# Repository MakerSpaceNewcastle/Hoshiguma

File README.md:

# Hoshiguma

Maker Space's shiny new laser cutter.

Docs Soon(TM).

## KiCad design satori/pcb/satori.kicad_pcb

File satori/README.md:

# Satori

This coprocessor is responsible for slow, low priority or unreliable machine safety signalling and networked reporting.

## Tasks

- Read cooling system temperature sensors
- Read cooling system flow sensor
- Receive machine status from Koishi via UART
- Report complete machine status and sensor values via MQTT

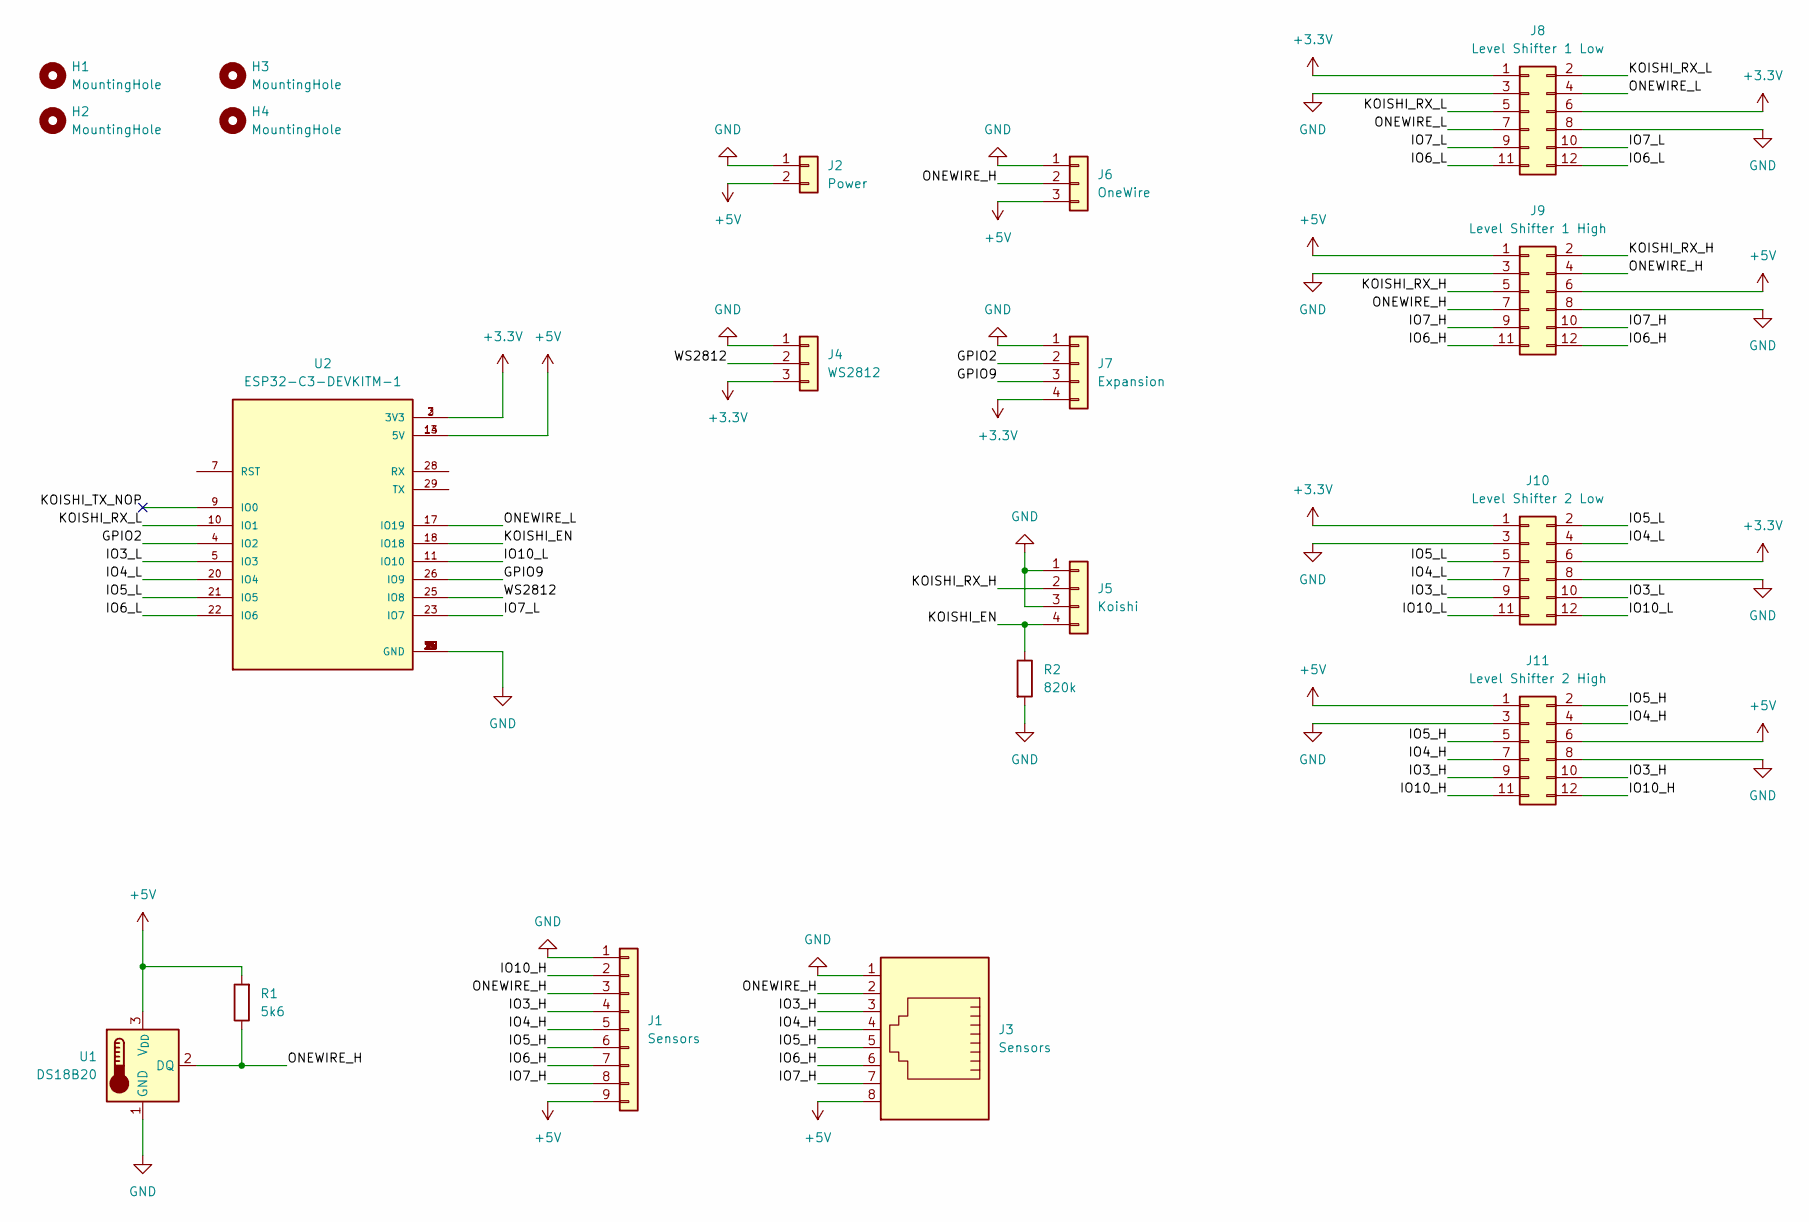
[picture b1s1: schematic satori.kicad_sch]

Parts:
H1, H2, H3, H4: MountingHole; MountingHole_3.2mm_M3
J1: Sensors; PinHeader_1x09_P2.54mm_Vertical
J2: Power; PinHeader_1x02_P2.54mm_Vertical
J3: Sensors; RJ45_Amphenol_54602-x08_Horizontal
J4: WS2812; PinHeader_1x03_P2.54mm_Vertical
J5: Koishi; PinHeader_1x04_P2.54mm_Vertical
J6: OneWire; PinHeader_1x03_P2.54mm_Vertical
J7: Expansion; PinHeader_1x04_P2.54mm_Vertical
J8: Level Shifter 1 Low; PinSocket_2x06_P2.54mm_Vertical
J9: Level Shifter 1 High; PinSocket_2x06_P2.54mm_Vertical
J10: Level Shifter 2 Low; PinSocket_2x06_P2.54mm_Vertical
J11: Level Shifter 2 High; PinSocket_2x06_P2.54mm_Vertical
R1: 5k6; R_Axial_DIN0207_L6.3mm_D2.5mm_P7.62mm_Horizontal
R2: 820k; R_Axial_DIN0207_L6.3mm_D2.5mm_P7.62mm_Horizontal
U1: DS18B20; TO-92_Inline
U2: ESP32-C3-DEVKITM-1; XCVR_ESP32-C3-DEVKITM-1

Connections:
+3.3V: J4.3, J7.4, J8.1, J8.6, J10.1, J10.6, U2.2 (3V3), U2.3 (3V3)
+5V: J1.9, J2.2, J3.8, J6.3, J9.1, J9.6, J11.1, J11.6, R1.2, U1.3 (V_{DD}), U2.13 (5V), U2.14 (5V)
/GPIO2: J7.2, U2.4 (IO2)
/GPIO9: J7.3, U2.26 (IO9)
/IO3_H: J1.4, J3.3, J11.9, J11.10
/IO3_L: J10.9, J10.10, U2.5 (IO3)
/IO4_H: J1.5, J3.4, J11.4, J11.7
/IO4_L: J10.4, J10.7, U2.20 (IO4)
/IO5_H: J1.6, J3.5, J11.2, J11.5
/IO5_L: J10.2, J10.5, U2.21 (IO5)
/IO6_H: J1.7, J3.6, J9.11, J9.12
/IO6_L: J8.11, J8.12, U2.22 (IO6)
/IO7_H: J1.8, J3.7, J9.9, J9.10
/IO7_L: J8.9, J8.10, U2.23 (IO7)
/IO10_H: J1.2, J11.11, J11.12
/IO10_L: J10.11, J10.12, U2.11 (IO10)
/KOISHI_EN: J5.4, R2.1, U2.18 (IO18)
/KOISHI_RX_H: J5.2, J9.2, J9.5
/KOISHI_RX_L: J8.2, J8.5, U2.10 (IO1)
/KOISHI_TX_NOP: U2.9 (IO0)
/ONEWIRE_H: J1.3, J3.2, J6.2, J9.4, J9.7, R1.1, U1.2 (DQ)
/ONEWIRE_L: J8.4, J8.7, U2.17 (IO19)
/WS2812: J4.2, U2.25 (IO8)
GND: J1.1, J2.1, J3.1, J4.1, J5.1, J5.3, J6.1, J7.1, J8.3, J8.8, J9.3, J9.8, J10.3, J10.8, J11.3, J11.8, R2.2, U1.1 (GND), U2.1 (GND), U2.6 (GND), U2.8 (GND), U2.12 (GND), U2.15 (GND), U2.16 (GND), U2.19 (GND), U2.24 (GND), U2.27 (GND), U2.30 (GND)

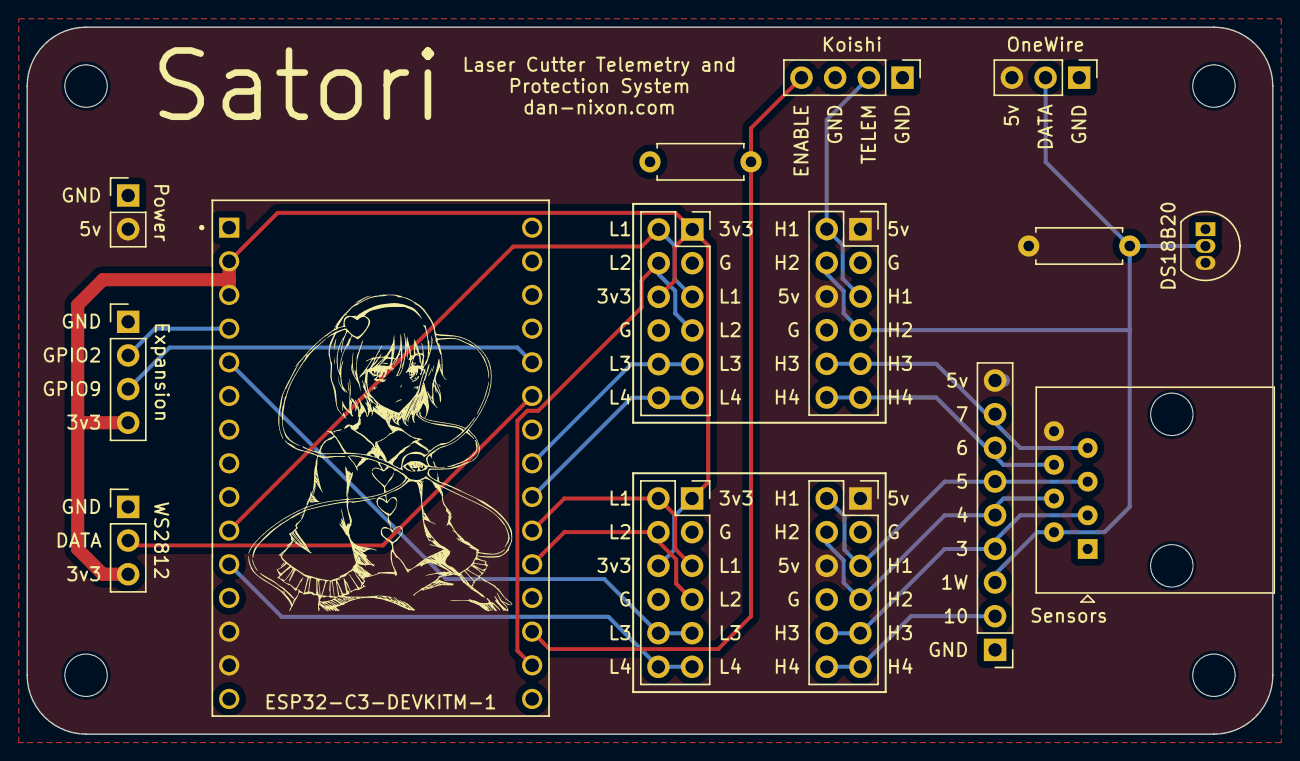
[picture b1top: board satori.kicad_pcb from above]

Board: 2 copper layers, 94.0 x 53.3 mm, 19 parts (0 on the bottom side), 23 nets.

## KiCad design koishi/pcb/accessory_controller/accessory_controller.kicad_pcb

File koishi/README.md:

# Koishi

This coprocessor is responsible for fast safety and machine control signalling only.

All inputs are via isolated digital pins. Serial input should not be used.

Outputs are via relays and status reporting via UART.

## Tasks

- Providing Ruida generic system protection signal
- Providing Ruida cooling protection signal
- Providing laser PSU protection signal
- Start/stop air assist compressor
- Start/stop fume extraction fan
- Illuminate machine status lights

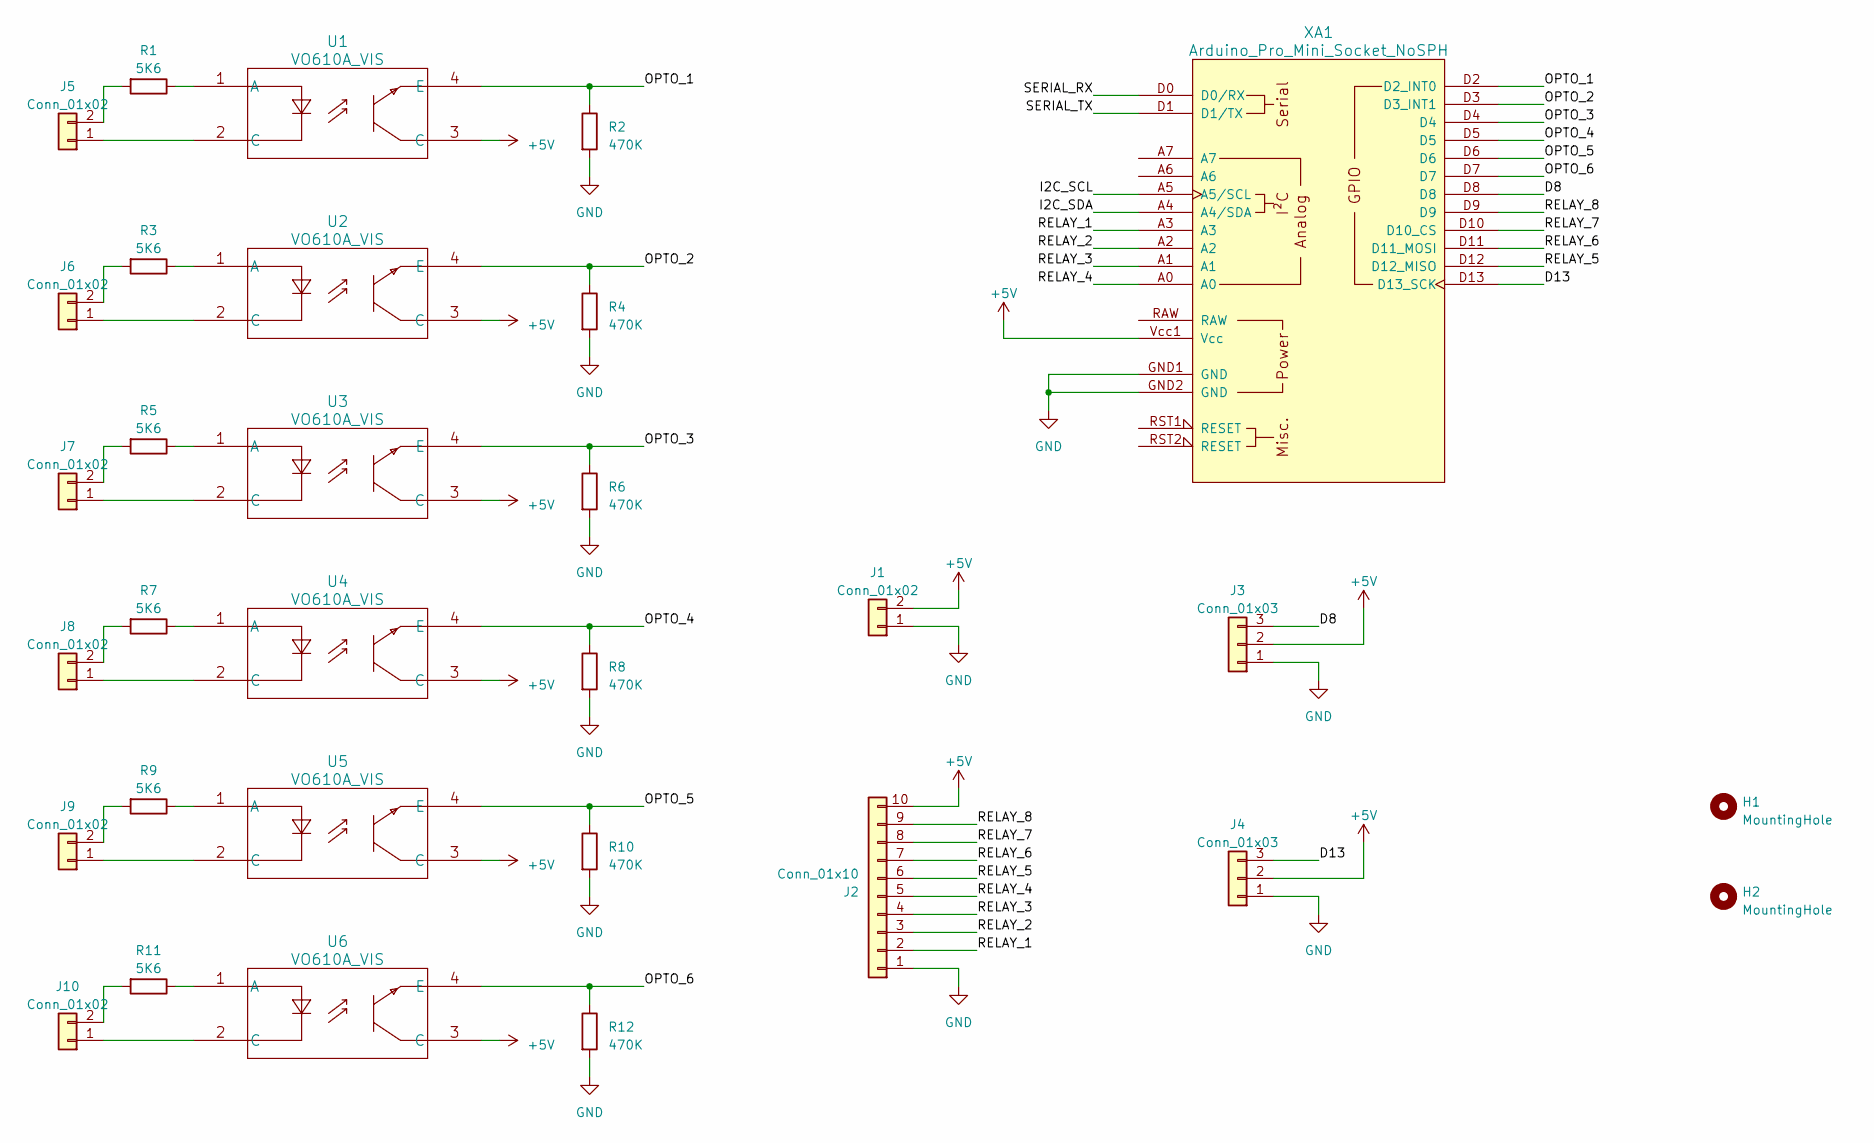
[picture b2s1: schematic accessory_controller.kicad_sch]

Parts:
H1, H2: MountingHole; MountingHole_4mm
J1, J5, J6, J7, J8, J9, J10: Conn_01x02; PinHeader_1x02_P2.54mm_Vertical
J2: Conn_01x10; PinSocket_1x10_P2.54mm_Vertical
J3, J4: Conn_01x03; PinHeader_1x03_P2.54mm_Vertical
R1, R3, R5, R7, R9, R11: 5K6; R_Axial_DIN0207_L6.3mm_D2.5mm_P2.54mm_Vertical
R2, R4, R6, R8, R10, R12: 470K; R_Axial_DIN0207_L6.3mm_D2.5mm_P2.54mm_Vertical
U1, U2, U3, U4, U5, U6: VO610A_VIS; VO610A-3
XA1: Arduino_Pro_Mini_Socket_NoSPH

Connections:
+5V: J1.2, J2.10, J3.2, J4.2, U1.3 (C), U2.3 (C), U3.3 (C), U4.3 (C), U5.3 (C), U6.3 (C), XA1.Vcc1 (Vcc)
/D8: J3.3, XA1.D8
/D13: J4.3, XA1.D13 (D13_SCK)
/I2C_SCL: XA1.A5 (A5/SCL)
/I2C_SDA: XA1.A4 (A4/SDA)
/OPTO_1: R2.1, U1.4 (E), XA1.D2 (D2_INT0)
/OPTO_2: R4.1, U2.4 (E), XA1.D3 (D3_INT1)
/OPTO_3: R6.1, U3.4 (E), XA1.D4
/OPTO_4: R8.1, U4.4 (E), XA1.D5
/OPTO_5: R10.1, U5.4 (E), XA1.D6
/OPTO_6: R12.1, U6.4 (E), XA1.D7
/RELAY_1: J2.2, XA1.A3
/RELAY_2: J2.3, XA1.A2
/RELAY_3: J2.4, XA1.A1
/RELAY_4: J2.5, XA1.A0
/RELAY_5: J2.6, XA1.D12 (D12_MISO)
/RELAY_6: J2.7, XA1.D11 (D11_MOSI)
/RELAY_7: J2.8, XA1.D10 (D10_CS)
/RELAY_8: J2.9, XA1.D9
/SERIAL_RX: XA1.D0 (D0/RX)
/SERIAL_TX: XA1.D1 (D1/TX)
GND: J1.1, J2.1, J3.1, J4.1, R2.2, R4.2, R6.2, R8.2, R10.2, R12.2, XA1.GND1 (GND), XA1.GND2 (GND)
unnamed: J5.1, U1.2 (C)
unnamed: J5.2, R1.2
unnamed: J6.1, U2.2 (C)
unnamed: J6.2, R3.2
unnamed: J7.1, U3.2 (C)
unnamed: J7.2, R5.2
unnamed: J8.1, U4.2 (C)
unnamed: J8.2, R7.2
unnamed: J9.1, U5.2 (C)
unnamed: J9.2, R9.2
unnamed: J10.1, U6.2 (C)
unnamed: J10.2, R11.2
unnamed: R1.1, U1.1 (A)
unnamed: R3.1, U2.1 (A)
unnamed: R5.1, U3.1 (A)
unnamed: R7.1, U4.1 (A)
unnamed: R9.1, U5.1 (A)
unnamed: R11.1, U6.1 (A)

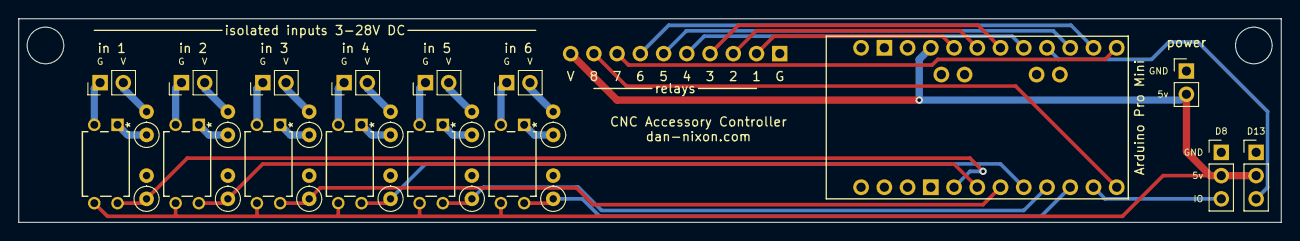
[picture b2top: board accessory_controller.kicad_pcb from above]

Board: 2 copper layers, 138.0 x 22.3 mm, 31 parts (1 on the bottom side), 36 nets.

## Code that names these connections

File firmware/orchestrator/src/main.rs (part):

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        relay: PIN_13, // Relay 6
    },
    unused_relays: UnusedRelayResources {
        relay_3: PIN_10,
        relay_7: PIN_14,
        relay_8: PIN_15,
    },
}

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
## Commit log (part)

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2025-10-01 build(deps): bump sntpc
    Bumps the cargo-dependencies group in /telemetry-module-firmware with 1 update: [sntpc](https://github.com/vpetrigo/sntpc).
    Updates `sntpc` from 0.6.0 to 0.6.1
    - [Release notes](https://github.com/vpetrigo/sntpc/releases)
    - [Commits](https://github.com/vpetrigo/sntpc/compare/v0.6.0...v0.6.1)
    ---
    updated-dependencies:
2025-10-01 build(deps): bump the cargo-dependencies group
    Bumps the cargo-dependencies group in /diagnostic-cli with 2 updates: [clap](https://github.com/clap-rs/clap) and [log](https://github.com/rust-lang/log).
    Updates `clap` from 4.5.46 to 4.5.48
    - [Release notes](https://github.com/clap-rs/clap/releases)
    - [Changelog](https://github.com/clap-rs/clap/blob/master/CHANGELOG.md)
    - [Commits](https://github.com/clap-rs/clap/compare/clap_complete-v4.5.46...clap_complete-v4.5.48)
    Updates `log` from 0.4.27 to 0.4.28
2025-10-03 build(deps): bump the cargo-dependencies group
    Bumps the cargo-dependencies group in /peripheral-controller-firmware with 2 updates: [pico-plc-bsp](https://github.com/DanNixon/pico-plc) and [embassy-executor](https://github.com/embassy-rs/embassy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
    Updates `pico-plc-bsp` from `884d18a` to `4f7a3f0`
    - [Commits](https://github.com/DanNixon/pico-plc/compare/884d18a6c678fd1a1f9453b51da200c5062dc2d3...4f7a3f0ae9bc2f35d2adf0af07f8615b6e6e88eb)
    Updates `embassy-executor` from 0.8.0 to 0.9.1
    - [Changelog](https://github.com/embassy-rs/embassy/blob/main/RELEASE.md)
    - [Commits](https://github.com/embassy-rs/embassy/compare/embassy-executor-v0.8.0...embassy-executor-v0.9.1)
2025-10-03 Update devenv module
2025-11-01 build(deps): bump defmt-rtt
    Bumps the cargo-dependencies group in /peripheral-controller-firmware with 1 update: [defmt-rtt](https://github.com/knurling-rs/defmt).
    Updates `defmt-rtt` from 1.0.0 to 1.1.0
    - [Release notes](https://github.com/knurling-rs/defmt/releases)
    - [Changelog](https://github.com/knurling-rs/defmt/blob/main/CHANGELOG.md)
    - [Commits](https://github.com/knurling-rs/defmt/compare/defmt-rtt-v1.0.0...defmt-rtt-v1.1.0)
    ---
2025-11-01 build(deps): bump defmt-rtt
    Bumps the cargo-dependencies group in /cooler-firmware with 1 update: [defmt-rtt](https://github.com/knurling-rs/defmt).
    Updates `defmt-rtt` from 1.0.0 to 1.1.0
    - [Release notes](https://github.com/knurling-rs/defmt/releases)
    - [Changelog](https://github.com/knurling-rs/defmt/blob/main/CHANGELOG.md)
    - [Commits](https://github.com/knurling-rs/defmt/compare/defmt-rtt-v1.0.0...defmt-rtt-v1.1.0)
    ---
2025-11-01 build(deps): bump the cargo-dependencies group
    Bumps the cargo-dependencies group in /telemetry-module-firmware with 2 updates: [defmt-rtt](https://github.com/knurling-rs/defmt) and [embedded-nal-async](https://github.com/rust-embedded-community/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
    Updates `defmt-rtt` from 1.0.0 to 1.1.0
    - [Release notes](https://github.com/knurling-rs/defmt/releases)
    - [Changelog](https://github.com/knurling-rs/defmt/blob/main/CHANGELOG.md)
    - [Commits](https://github.com/knurling-rs/defmt/compare/defmt-rtt-v1.0.0...defmt-rtt-v1.1.0)
    Updates `embedded-nal-async` from 0.8.0 to 0.9.0
2025-11-01 Update crates
2025-11-01 build(deps): bump embedded-nal-async
    Bumps the cargo-dependencies group with 1 update in the /telemetry-module-firmware directory: [embedded-nal-async](https://github.com/rust-embedded-community/embedded-nal).
    Updates `embedded-nal-async` from 0.8.0 to 0.9.0
    - [Release notes](https://github.com/rust-embedded-community/embedded-nal/releases)
    - [Changelog](https://github.com/rust-embedded-community/embedded-nal/blob/master/CHANGELOG.md)
    - [Commits](https://github.com/rust-embedded-community/embedded-nal/compare/embedded-nal-async-v0.8.0...embedded-nal-async-v0.9.0)
    ---
2025-11-07 Remove Pico W wifi firmware blobs
2025-11-09 Add fume extraction airflow measurement (#153)
2025-11-17 Allow more retires after accessory bus communication failure
2025-11-27 Be more lenient of the airflow sensor not responding
2025-12-01 build(deps): bump actions/checkout from 5 to 6
    Bumps [actions/checkout](https://github.com/actions/checkout) from 5 to 6.
    - [Release notes](https://github.com/actions/checkout/releases)
    - [Changelog](https://github.com/actions/checkout/blob/main/CHANGELOG.md)
    - [Commits](https://github.com/actions/checkout/compare/v5...v6)
    ---
    updated-dependencies:
2025-12-01 build(deps): bump heapless
    Bumps the cargo-dependencies group in /peripheral-controller-firmware with 1 update: [heapless](https://github.com/rust-embedded/heapless).
    Updates `heapless` from 0.9.1 to 0.9.2
    - [Release notes](https://github.com/rust-embedded/heapless/releases)
    - [Changelog](https://github.com/rust-embedded/heapless/blob/main/CHANGELOG.md)
    - [Commits](https://github.com/rust-embedded/heapless/commits)
    ---
2025-12-01 Update crates and Rust version
2025-12-05 build(deps): bump log
    Bumps the cargo-dependencies group with 1 update in the /diagnostic-cli directory: [log](https://github.com/rust-lang/log).
    Updates `log` from 0.4.28 to 0.4.29
    - [Release notes](https://github.com/rust-lang/log/releases)
    - [Changelog](https://github.com/rust-lang/log/blob/master/CHANGELOG.md)
    - [Commits](https://github.com/rust-lang/log/compare/0.4.28...0.4.29)
    ---
2025-12-05 build(deps): bump the cargo-dependencies group
    Bumps the cargo-dependencies group in /telemetry-module-firmware with 2 updates: [embassy-rp](https://github.com/embassy-rs/embassy) and [sntpc](https://github.com/vpetrigo/sntpc).
    Updates `embassy-rp` from 0.8.0 to 0.9.0
    - [Changelog](https://github.com/embassy-rs/embassy/blob/main/RELEASE.md)
    - [Commits](https://github.com/embassy-rs/embassy/compare/embassy-rp-v0.8.0...embassy-rp-v0.9.0)
    Updates `sntpc` from 0.6.1 to 0.7.0
    - [Release notes](https://github.com/vpetrigo/sntpc/releases)
2025-12-05 Reduce telemetry transmit delay
2025-12-11 Use `spawner.must_spawn(...)` in place of `unwrap!(spawner.spawn(...))`
2026-01-01 build(deps): bump pico-plc-bsp
    Bumps the cargo-dependencies group in /cooler-firmware with 1 update: [pico-plc-bsp](https://github.com/DanNixon/pico-plc).
    Updates `pico-plc-bsp` from `a093d6f` to `858373b`
    - [Commits](https://github.com/DanNixon/pico-plc/compare/a093d6f04e57d45b71a490a610e6b7d30ceaeab1...858373b3598c8b32888e172455651fdd23ce4415)
    ---
    updated-dependencies:
    - dependency-name: pico-plc-bsp
2026-01-01 build(deps): bump the cargo-dependencies group
    Bumps the cargo-dependencies group in /telemetry-module-firmware with 2 updates: [embedded-nal-async](https://github.com/rust-embedded-community/embedded-nal) and [portable-atomic](https://github.com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
    Updates `embedded-nal-async` from 0.8.0 to 0.9.0
    - [Release notes](https://github.com/rust-embedded-community/embedded-nal/releases)
    - [Changelog](https://github.com/rust-embedded-community/embedded-nal/blob/master/CHANGELOG.md)
    - [Commits](https://github.com/rust-embedded-community/embedded-nal/compare/embedded-nal-async-v0.8.0...embedded-nal-async-v0.9.0)
    Updates `portable-atomic` from 1.11.1 to 1.13.0
2026-01-01 Move Dependabot to quarterly
2026-01-01 Combine all Cargo Dependabot updates into a single PR
2026-01-01 build(deps): bump the cargo-dependencies group across 4 directories with 4 updates
    Bumps the cargo-dependencies group with 1 update in the /cooler-firmware directory: [pico-plc-bsp](https://github.com/DanNixon/pico-plc).
    Bumps the cargo-dependencies group with 2 updates in the /extraction-airflow-sensor-firmware directory: [embassy-rp](https://github.com/embassy-rs/embassy) and [portable-atomic](https://github.com/ta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
    Bumps the cargo-dependencies group with 1 update in the /peripheral-controller-firmware directory: [portable-atomic](https://github.com/taiki-e/portable-atomic).
    Bumps the cargo-dependencies group with 2 updates in the /telemetry-module-firmware directory:
2026-01-01 build(deps): bump the cargo-dependencies group across 4 directories with 3 updates
    Bumps the cargo-dependencies group with 1 update in the /cooler-firmware directory: [pico-plc-bsp](https://github.com/DanNixon/pico-plc).
    Bumps the cargo-dependencies group with 2 updates in the /extraction-airflow-sensor-firmware directory: [embassy-rp](https://github.com/embassy-rs/embassy) and [portable-atomic](https://github.com/ta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
    Bumps the cargo-dependencies group with 1 update in the /peripheral-controller-firmware directory: [portable-atomic](https://github.com/taiki-e/portable-atomic).
    Bumps the cargo-dependencies group with 1 update in the /telemetry-module-firmware directory:
2026-01-10 Add CLI to peripheral controller
2026-01-10 Remove diagnostic-cli
2026-01-12 New access controller
2026-01-12 Remove unused flake dependencies
2026-01-14 Add information severity for non-critical states
2026-01-14 Allow disabling network in telemetry module
    Useful for debugging
2026-01-15 Add typos
2026-01-16 Move all crates to 2024 edition and reformat
2026-01-16 New front/control panel
2026-01-24 Update machine settings
    - disable auto focus
    - apparenetly lots of other things I set on the machine and did not update this file
2026-01-24 Add manual focus tool for switch back to manual focusing
2026-01-27 Switch runner from ubuntu-latest to ubuntu-slim for formatting CI
2026-02-07 Refactor telementry and shared crate
2026-02-14 Restructure firmware projects
2026-02-14 build(deps): bump the cargo-dependencies group across 3 directories with 3 updates
    Bumps the cargo-dependencies group with 2 updates in the /firmware/cooler directory: [pico-plc-bsp](https://github.com/DanNixon/pico-plc) and [teeny-rpc](https://github.com/DanNixon/teeny-rpc).
    Bumps the cargo-dependencies group with 3 updates in the /firmware/orchestrator directory: [pico-plc-bsp](https://github.com/DanNixon/pico-plc), [teeny-rpc](https://github.com/DanNixon/teeny-rpc) and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
    Bumps the cargo-dependencies group with 1 update in the /firmware/telemetry-bridge directory: [teeny-rpc](https://github.com/DanNixon/teeny-rpc).
    Updates `pic
2026-02-14 Remove use of pico-plc-bsp from cooler firmware
2026-02-16 build(deps): bump the cargo-dependencies group across 3 directories with 2 updates
    Bumps the cargo-dependencies group with 2 updates in the /firmware/cooler directory: [portable-atomic](https://github.com/taiki-e/portable-atomic) and [teeny-rpc](https://github.com/DanNixon/teeny-rp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
    Bumps the cargo-dependencies group with 2 updates in the /firmware/orchestrator directory: [portable-atomic](https://github.com/taiki-e/portable-atomic) and [teeny-rpc](https://github.com/DanNixon/te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
    Bumps the cargo-dependencies group with 1 update in the /firmware/telemetry-bridge directory: [teeny-rpc](https://github.com/DanNixon/teeny-rpc).
    Updates `portable-atomic` from 1.13.0 to 1.13.1
    - [Releas
2026-02-20 build(deps): bump keccak in /firmware/extraction-airflow-sensor
    Bumps [keccak](https://github.com/RustCrypto/sponges) from 0.1.5 to 0.1.6.
    - [Commits](https://github.com/RustCrypto/sponges/compare/keccak-v0.1.5...keccak-v0.1.6)
    ---
    updated-dependencies:
    - dependency-name: keccak
    dependency-version: 0.1.6
2026-02-27 pins
2026-03-21 New reservoir temperature sensor
2026-04-01 build(deps): bump DeterminateSystems/nix-installer-action from 21 to 22
    Bumps [DeterminateSystems/nix-installer-action](https://github.com/determinatesystems/nix-installer-action) from 21 to 22.
    - [Release notes](https://github.com/determinatesystems/nix-installer-action/releases)
    - [Commits](https://github.com/determinatesystems/nix-installer-action/compare/v21...v22)
    ---
    updated-dependencies:
    - dependency-name: DeterminateSystems/nix-installer-action
2026-04-01 build(deps): bump keccak in /firmware/telemetry-bridge
    Bumps [keccak](https://github.com/RustCrypto/sponges) from 0.1.5 to 0.1.6.
    - [Commits](https://github.com/RustCrypto/sponges/compare/keccak-v0.1.5...keccak-v0.1.6)
    ---
    updated-dependencies:
    - dependency-name: keccak
    dependency-version: 0.1.6
2026-04-20 Generalize bidirectional channel API
    Split message type parameter into AToB/BToA, rename Side fields
    from inbox/outbox to to_me/to_you, and update call sites to the new API.
2026-04-25 tidy cad
2026-04-25 Use Ethernet/UDP connection for controller
2026-04-26 Extract Message into api::message module

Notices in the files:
parts and their libraries:
Copyright 2016 Accelerated Designs. All rights reserved.
